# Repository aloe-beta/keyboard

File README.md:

# Keyboard

A low-profile split keyboard with 56 hotswappable, RGB backlit keys. Powered by an ESP32-S3.

This is the first project I'm trying to get a PCB manufactured for. I've polished the design up to a point I'm happy with, but there might be mistakes.

The directory structure should be self-explanatory. Currently, `firmare/` only contains a blink program. I'm still deciding whether I should try porting ZMK (ESP32-S3 requires some work) or writing my own firmware from scratch. The latter option would give me more freedom to experiment with the hardware (I have some unconventional ideas), so I'm leaning towards that.

The BOM does not contain anything for the housing or keycaps, as I intend to resin-print those myself.

**Schematic:**

**PCB:**

**Housing:**

**Keycaps:**

**BOM:**

| Name                                            | Description                                                           | Reference | Link                                                                                                          | Quantity | Unit quantity | Unit price     | Total price | Seller  |
| ----------------------------------------------- | --------------------------------------------------------------------- | --------- | ------------------------------------------------------------------------------------------------------------- | -------- | ------------- | -------------- | ----------- | ------- |
| 3.7V 1000mAh 502450 Lipo                        | Battery                                                               | N/A       | https://www.amazon.com/dp/B07BTV3W87                                                                          | 2        | 2             | 7.4900         | 14.98       | Amazon  |
| CL31A107MQHNNWE                                 | 100uF capacitor for the LEDs                                          | C1-C2     | https://www.digikey.com/en/products/detail/samsung-electro-mechanics/CL31A107MQHNNWE/10479833                 | 2        | 2             | 0.4000         | 0.80        | DigiKey |
| MSE1PG-M3                                       | Diodes for use in the wired interconnect                              | D113-D114 | https://www.digikey.com/en/products/detail/vishay-general-semiconductor-diodes-division/MSE1PG-M3-89A/2149917 | 2        | 2             | 0.1000         | 0.20        | DigiKey |
| 5149-LSH-3956D-005-G-19CT-ND                    | TRRS jacks for wired interconnect                                     | J1-J2     | https://www.digikey.com/en/products/detail/linkplex/LSH-3956D-005-G-19/26798666                               | 2        | 2             | 0.9900         | 1.98        | DigiKey |
| 4786-GSFC02501CT-ND                             | P-channel MOSFETs to toggle power to the LEDs and wired interconnect. | Q1-Q4     | https://www.digikey.com/en/products/detail/good-ark-semiconductor/GSFC02501/18648296                          | 4        | 10            | 0.0390         | 0.39        | DigiKey |
| 311-390GRCT-ND                                  | 390 ohm resistors for the first neopixel input lines                  | R1-R2     | https://www.digikey.com/en/products/detail/yageo/RC0603JR-07390RL/726777                                      | 2        | 10            | 0.0070         | 0.07        | DigiKey |
| 311-10.0KFRCT-ND                                | 10k ohm pull-up/pull-down resistors for MOSFET circuits               | R3-R10    | https://www.digikey.com/en/products/detail/yageo/RC1206FR-0710KL/728483                                       | 8        | 10            | 0.0180         | 0.18        | DigiKey |
| 455-1719-ND                                     | JST battery connector                                                 | TP1-TP2   | https://www.digikey.com/en/products/detail/jst-sales-america-inc/S2B-PH-K-S/926626                            | 2        | 2             | 0.1000         | 0.20        | DigiKey |
| Seeed Studio XIAO ESP32-S3                      | MCU                                                                   | U3-U4     | https://www.digikey.com/en/products/detail/seeed-technology-co-ltd/113991114/19285530                         | 2        | 2             | 7.4900         | 14.98       | DigiKey |
| GATERON Upgrade Hot-swap PCB 2.0 Socket         | Hotswappable switch bracket                                           | SW1-SW56  | https://www.gateron.com/products/gateron-hot-swap-pcb-socket?VariantsId=10170                                 | 56       | 1x70          | 7.0000         | 7.00        | Gateron |
| GATERON KS-33 Low Profile 2.0 Mechanical Switch | Low-profile mechanical switch                                         | N/A       | https://www.gateron.com/products/gateron-ks-33-low-profile-switch-set?VariantsId=11464                        | 56       | 2x35          | 9.8000         | 19.60       | Gateron |
| PCB                                             | The circuit board for the keyboard.                                   | N/A       | N/A                                                                                                           | 1        | 1x5           | 21.8600        | 11.00       | JLC     |
| Stencil                                         | The stencil for soldering the board.                                  | N/A       | N/A                                                                                                           | 1        | 1             | 7.0000         | 7.00        | JLC     |
| 1N4148W                                         | Diodes to prevent key ghosting                                        | D1-D56    | https://www.lcsc.com/product-detail/C51953478.html                                                            | 56       | 56            | 0.0430         | 2.41        | LCSC    |
| SK6812MINI-E                                    | Addressable RGB LEDs for the backlight                                | D57-D112  | https://www.lcsc.com/product-detail/C5149201.html                                                             | 56       | 60            | 0.0683         | 4.10        | LCSC    |
| SK12D07VG5                                      | Power switches                                                        | SW57-SW58 | https://www.lcsc.com/product-detail/C3020419.html                                                             | 2        | 20            | 0.0210         | 0.42        | LCSC    |
|                                                 |                                                                       |           |                                                                                                               |          |               | Tariffs        | 1.50        | DigiKey |
|                                                 |                                                                       |           |                                                                                                               |          |               | Shipping       | 4.99        | DigiKey |
|                                                 |                                                                       |           |                                                                                                               |          |               | Service Charge | 1.55        | Gateron |
|                                                 |                                                                       |           |                                                                                                               |          |               | Shipping       | 8.60        | Gateron |
|                                                 |                                                                       |           |                                                                                                               |          |               | Shipping       | 29.22       | JLC     |
|                                                 |                                                                       |           |                                                                                                               |          |               | Handling Fee   | 3.00        | LCSC    |
|                                                 |                                                                       |           |                                                                                                               |          |               | Shipping       | 8.42        | LCSC    |
|                                                 |                                                                       |           |                                                                                                               |          |               | Sales Tax      | 7.84        |         |
|                                                 |                                                                       |           |                                                                                                               |          |               | Total          | 150.43      |         |

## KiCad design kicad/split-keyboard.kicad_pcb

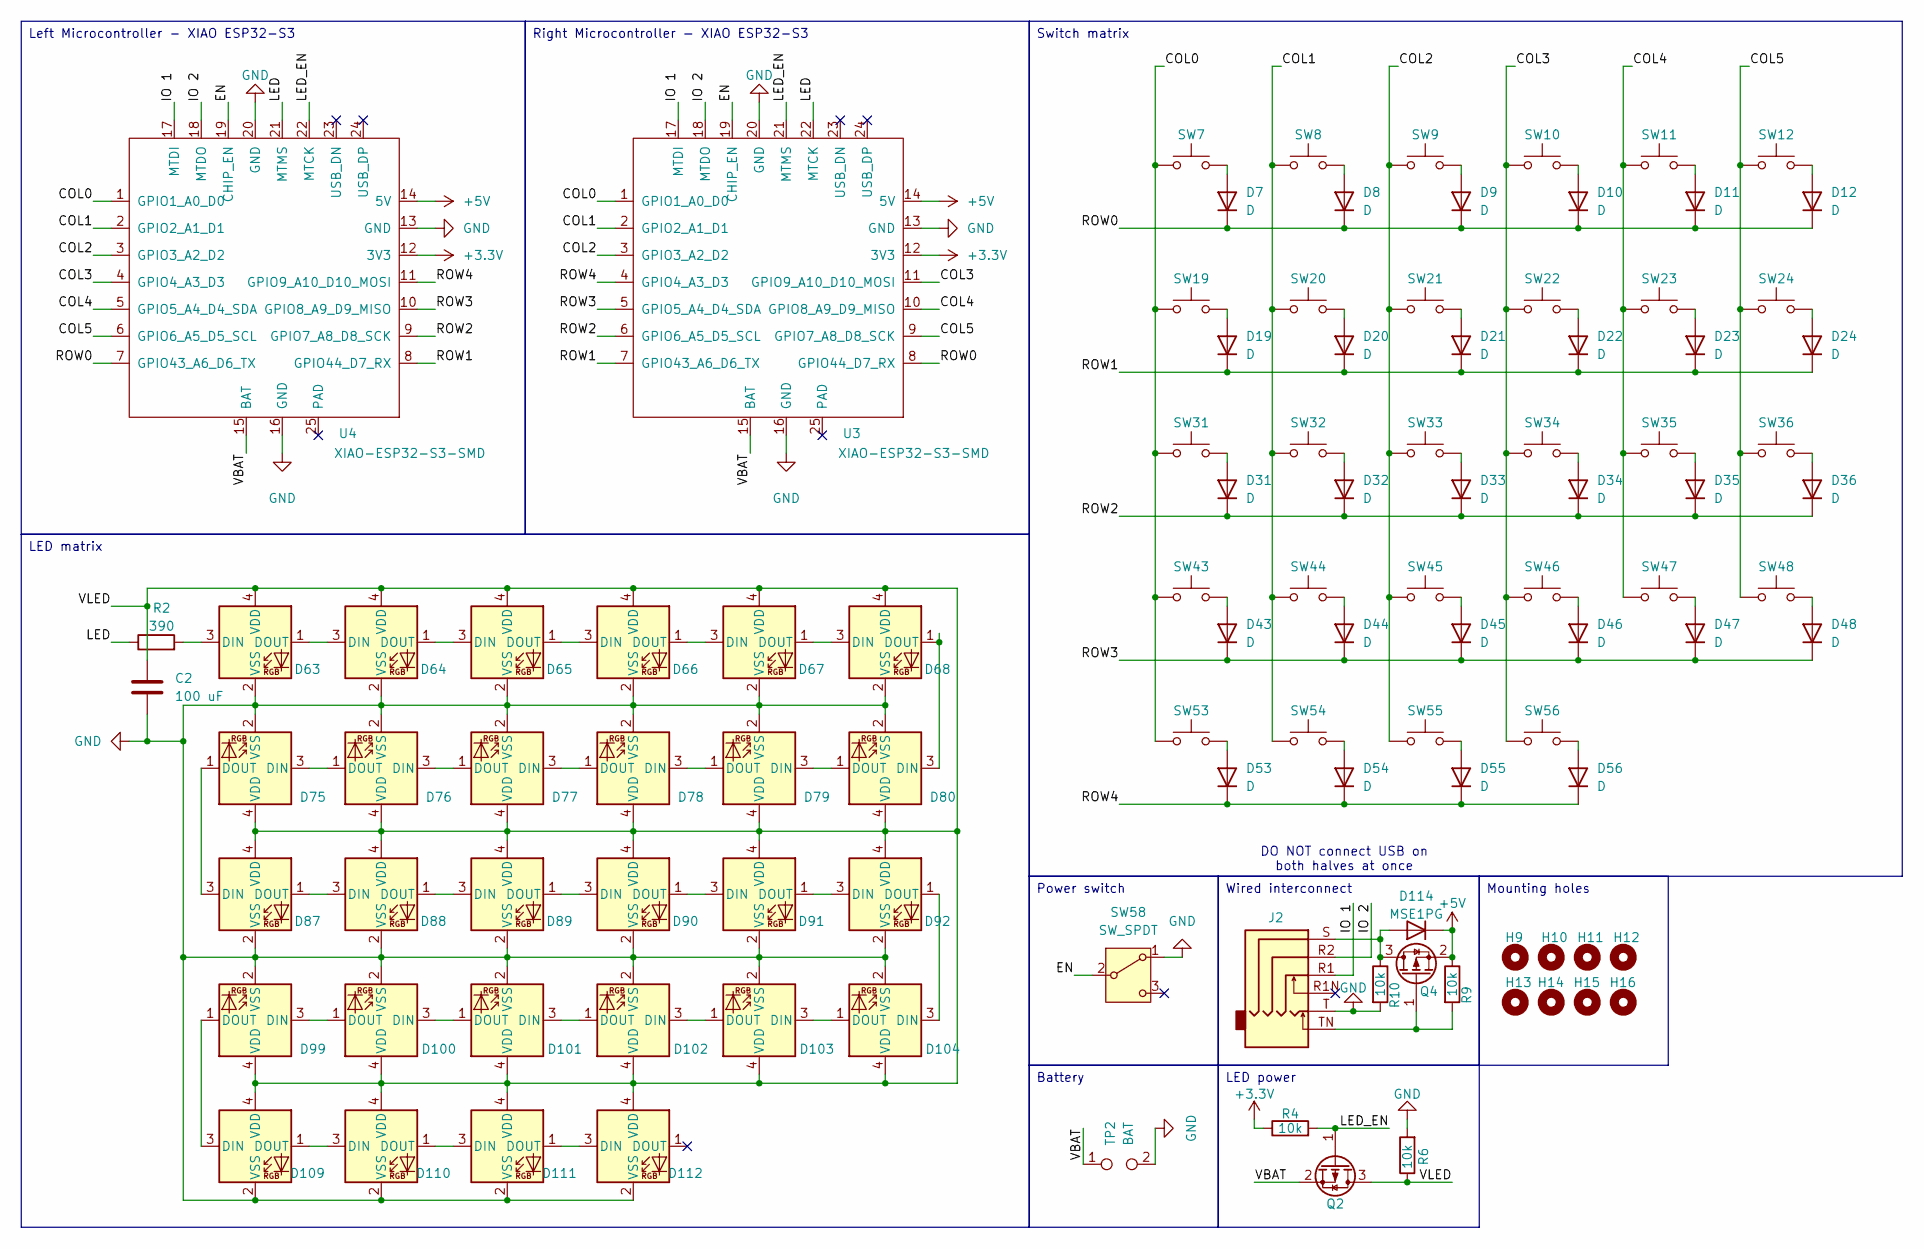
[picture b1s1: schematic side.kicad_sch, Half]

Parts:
C2: 100 uF; C_1206_3216Metric; LCSC C22399655
D7, D8, D9, D10, D11, D12, D19, D20, D21, D22, D23, D24, D31, D32, D33, D34, D35, D36, D43, D44, D45, D46, D47, D48, D53, D54, D55, D56: D; D_SOD-123; LCSC C169491
D63, D64, D65, D66, D67, D68, D75, D76, D77, D78, D79, D80, D87, D88, D89, D90, D91, D92, D99, D100, D101, D102, D103, D104, D109, D110, D111, D112: SK6812MINI; SK6812MINI-E_1-REV; LCSC C5149201
D114: MSE1PG; D_MicroSMP_AK; LCSC C94470
H9, H10, H11, H12, H13, H14, H15, H16: MountingHole; MountingHole_2.2mm_M2
J2: AudioJack4_SwitchTR1; LSH-3956D
Q2, Q4: Q_PMOS_GSD; SOT-23; LCSC C2589
R2: 390; R_0603_1608Metric; LCSC C190196
R4, R6, R9, R10: 10k; R_1206_3216Metric; LCSC C702844
SW7, SW8, SW9, SW10, SW11, SW12, SW19, SW20, SW21, SW22, SW23, SW24, SW31, SW32, SW33, SW34, SW35, SW36, SW43, SW44, SW45, SW46, SW47, SW48, SW53, SW54, SW55, SW56: SW_Push; SW_KS33_HS_KS-2P02B01-02_HS_1u; LCSC C9900205432
SW58: SW_SPDT; SK12D07VG5; LCSC C2896621
TP2: BAT; JST_PH_S2B-PH-K_1x02_P2.00mm_Horizontal; LCSC C173752
U3, U4: XIAO-ESP32-S3-SMD; XIAO-ESP32S3-SMD; LCSC C9900124959

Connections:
+3.3V: R4.1, U3.12 (3V3), U4.12 (3V3)
+5V: D114.1 (K), Q4.2 (S), R9.1, U3.14 (5V), U4.14 (5V)
/right/COL0: SW7.1, SW19.1, SW31.1, SW43.1, SW53.1, U3.1 (GPIO1_A0_D0), U4.1 (GPIO1_A0_D0)
/right/COL1: SW8.1, SW20.1, SW32.1, SW44.1, SW54.1, U3.2 (GPIO2_A1_D1), U4.2 (GPIO2_A1_D1)
/right/COL2: SW9.1, SW21.1, SW33.1, SW45.1, SW55.1, U3.3 (GPIO3_A2_D2), U4.3 (GPIO3_A2_D2)
/right/COL3: SW10.1, SW22.1, SW34.1, SW46.1, SW56.1, U3.11 (GPIO9_A10_D10_MOSI), U4.4 (GPIO4_A3_D3)
/right/COL4: SW11.1, SW23.1, SW35.1, SW47.1, U3.10 (GPIO8_A9_D9_MISO), U4.5 (GPIO5_A4_D4_SDA)
/right/COL5: SW12.1, SW24.1, SW36.1, SW48.1, U3.9 (GPIO7_A8_D8_SCK), U4.6 (GPIO6_A5_D5_SCL)
/right/EN: SW58.2 (B), U3.19 (CHIP_EN), U4.19 (CHIP_EN)
/right/IO 1: J2.R1, U3.17 (MTDI), U4.17 (MTDI)
/right/IO 2: J2.R2, U3.18 (MTDO), U4.18 (MTDO)
/right/LED: R2.1, U3.22 (MTCK), U4.21 (MTMS)
/right/LED_EN: Q2.1 (G), R4.2, U3.21 (MTMS), U4.22 (MTCK)
/right/ROW0: D7.1 (K), D8.1 (K), D9.1 (K), D10.1 (K), D11.1 (K), D12.1 (K), U3.8 (GPIO44_D7_RX), U4.7 (GPIO43_A6_D6_TX)
/right/ROW1: D19.1 (K), D20.1 (K), D21.1 (K), D22.1 (K), D23.1 (K), D24.1 (K), U3.7 (GPIO43_A6_D6_TX), U4.8 (GPIO44_D7_RX)
/right/ROW2: D31.1 (K), D32.1 (K), D33.1 (K), D34.1 (K), D35.1 (K), D36.1 (K), U3.6 (GPIO6_A5_D5_SCL), U4.9 (GPIO7_A8_D8_SCK)
/right/ROW3: D43.1 (K), D44.1 (K), D45.1 (K), D46.1 (K), D47.1 (K), D48.1 (K), U3.5 (GPIO5_A4_D4_SDA), U4.10 (GPIO8_A9_D9_MISO)
/right/ROW4: D53.1 (K), D54.1 (K), D55.1 (K), D56.1 (K), U3.4 (GPIO4_A3_D3), U4.11 (GPIO9_A10_D10_MOSI)
/right/VBAT: Q2.2 (S), TP2.1, U3.15 (BAT), U4.15 (BAT)
/right/VLED: C2.1, D63.4 (VDD), D64.4 (VDD), D65.4 (VDD), D66.4 (VDD), D67.4 (VDD), D68.4 (VDD), D75.4 (VDD), D76.4 (VDD), D77.4 (VDD), D78.4 (VDD), D79.4 (VDD), D80.4 (VDD), D87.4 (VDD), D88.4 (VDD), D89.4 (VDD), D90.4 (VDD), D91.4 (VDD), D92.4 (VDD), D99.4 (VDD), D100.4 (VDD), D101.4 (VDD), D102.4 (VDD), D103.4 (VDD), D104.4 (VDD), D109.4 (VDD), D110.4 (VDD), D111.4 (VDD), D112.4 (VDD), Q2.3 (D), R6.1
GND: C2.2, D63.2 (VSS), D64.2 (VSS), D65.2 (VSS), D66.2 (VSS), D67.2 (VSS), D68.2 (VSS), D75.2 (VSS), D76.2 (VSS), D77.2 (VSS), D78.2 (VSS), D79.2 (VSS), D80.2 (VSS), D87.2 (VSS), D88.2 (VSS), D89.2 (VSS), D90.2 (VSS), D91.2 (VSS), D92.2 (VSS), D99.2 (VSS), D100.2 (VSS), D101.2 (VSS), D102.2 (VSS), D103.2 (VSS), D104.2 (VSS), D109.2 (VSS), D110.2 (VSS), D111.2 (VSS), D112.2 (VSS), J2.T, R6.2, R10.2, SW58.1 (A), TP2.2, U3.13 (GND), U3.16 (GND), U3.20 (GND), U4.13 (GND), U4.16 (GND), U4.20 (GND)
unnamed: D7.2 (A), SW7.2
unnamed: D8.2 (A), SW8.2
unnamed: D9.2 (A), SW9.2
unnamed: D10.2 (A), SW10.2
unnamed: D11.2 (A), SW11.2
unnamed: D12.2 (A), SW12.2
unnamed: D19.2 (A), SW19.2
unnamed: D20.2 (A), SW20.2
unnamed: D21.2 (A), SW21.2
unnamed: D22.2 (A), SW22.2
unnamed: D23.2 (A), SW23.2
unnamed: D24.2 (A), SW24.2
unnamed: D31.2 (A), SW31.2
unnamed: D32.2 (A), SW32.2
unnamed: D33.2 (A), SW33.2
unnamed: D34.2 (A), SW34.2
unnamed: D35.2 (A), SW35.2
unnamed: D36.2 (A), SW36.2
unnamed: D43.2 (A), SW43.2
unnamed: D44.2 (A), SW44.2
unnamed: D45.2 (A), SW45.2
unnamed: D46.2 (A), SW46.2
unnamed: D47.2 (A), SW47.2
unnamed: D48.2 (A), SW48.2
unnamed: D53.2 (A), SW53.2
unnamed: D54.2 (A), SW54.2
unnamed: D55.2 (A), SW55.2
unnamed: D56.2 (A), SW56.2
unnamed: D63.3 (DIN), R2.2
unnamed: D63.1 (DOUT), D64.3 (DIN)
unnamed: D64.1 (DOUT), D65.3 (DIN)
unnamed: D65.1 (DOUT), D66.3 (DIN)
unnamed: D66.1 (DOUT), D67.3 (DIN)
unnamed: D67.1 (DOUT), D68.3 (DIN)
unnamed: D68.1 (DOUT), D80.3 (DIN)
unnamed: D75.3 (DIN), D76.1 (DOUT)
unnamed: D75.1 (DOUT), D87.3 (DIN)
unnamed: D76.3 (DIN), D77.1 (DOUT)
unnamed: D77.3 (DIN), D78.1 (DOUT)
unnamed: D78.3 (DIN), D79.1 (DOUT)
unnamed: D79.3 (DIN), D80.1 (DOUT)
unnamed: D87.1 (DOUT), D88.3 (DIN)
unnamed: D88.1 (DOUT), D89.3 (DIN)
unnamed: D89.1 (DOUT), D90.3 (DIN)
unnamed: D90.1 (DOUT), D91.3 (DIN)
unnamed: D91.1 (DOUT), D92.3 (DIN)
unnamed: D100.3 (DIN), D101.1 (DOUT)
unnamed: D99.3 (DIN), D100.1 (DOUT)
unnamed: D101.3 (DIN), D102.1 (DOUT)
unnamed: D102.3 (DIN), D103.1 (DOUT)
unnamed: D103.3 (DIN), D104.1 (DOUT)
unnamed: D92.1 (DOUT), D104.3 (DIN)
unnamed: D99.1 (DOUT), D109.3 (DIN)
unnamed: D109.1 (DOUT), D110.3 (DIN)
unnamed: D110.1 (DOUT), D111.3 (DIN)
unnamed: D111.1 (DOUT), D112.3 (DIN)
unnamed: D114.2 (A), J2.S, Q4.3 (D), R10.1
unnamed: J2.TN, Q4.1 (G), R9.2

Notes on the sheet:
DO NOT connect USB on both halves at once
Switch matrix
Wired interconnect
Battery
Right Microcontroller - XIAO ESP32-S3
Left Microcontroller - XIAO ESP32-S3
LED power
Power switch
LED matrix
Mounting holes

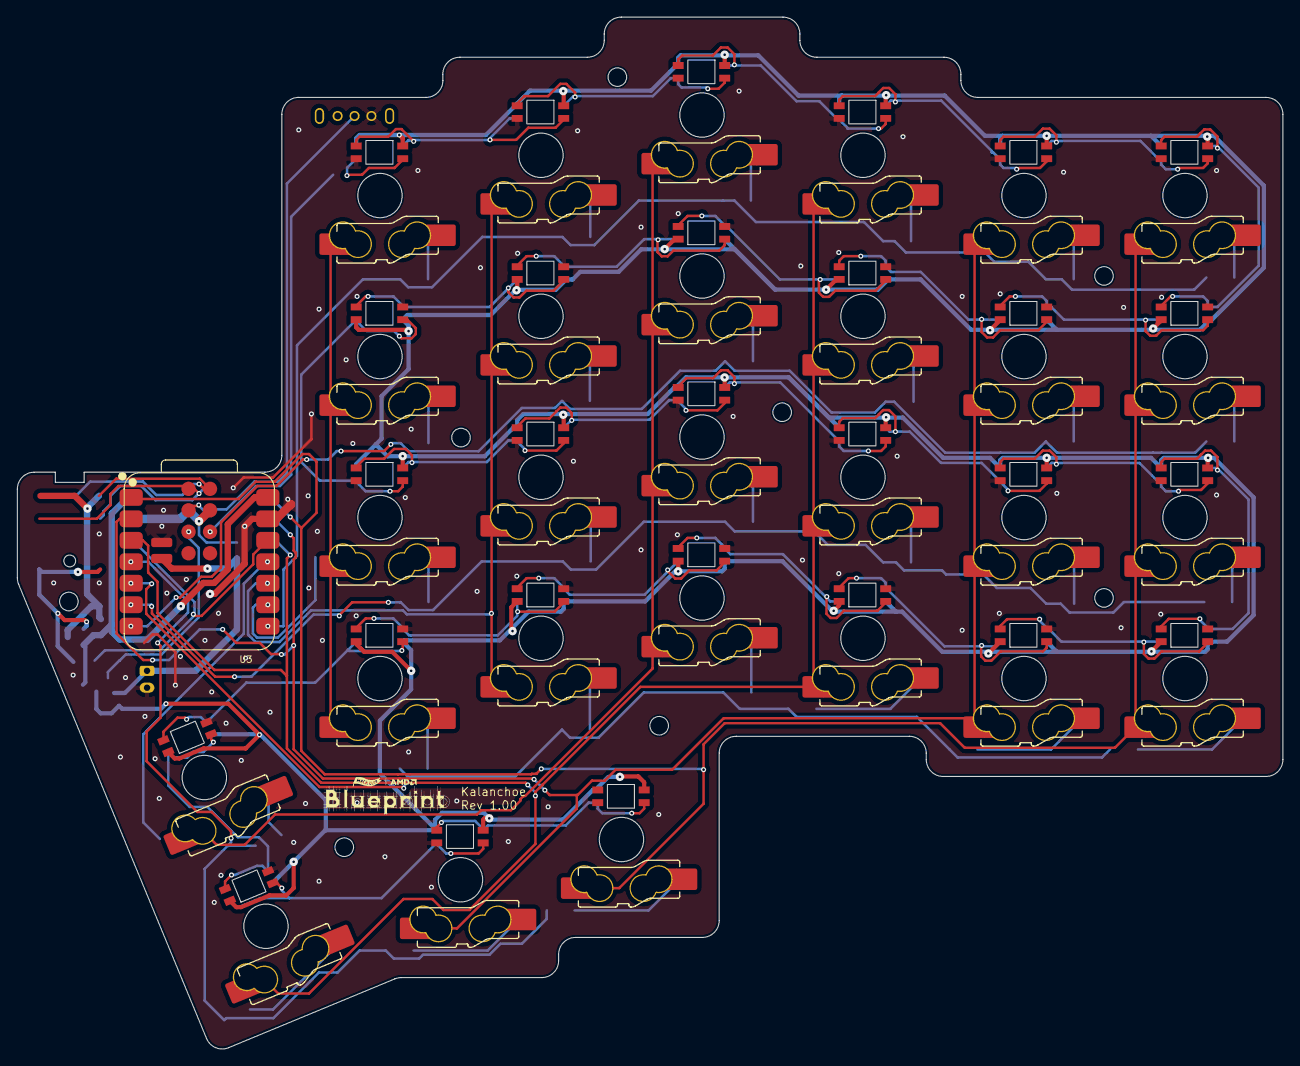
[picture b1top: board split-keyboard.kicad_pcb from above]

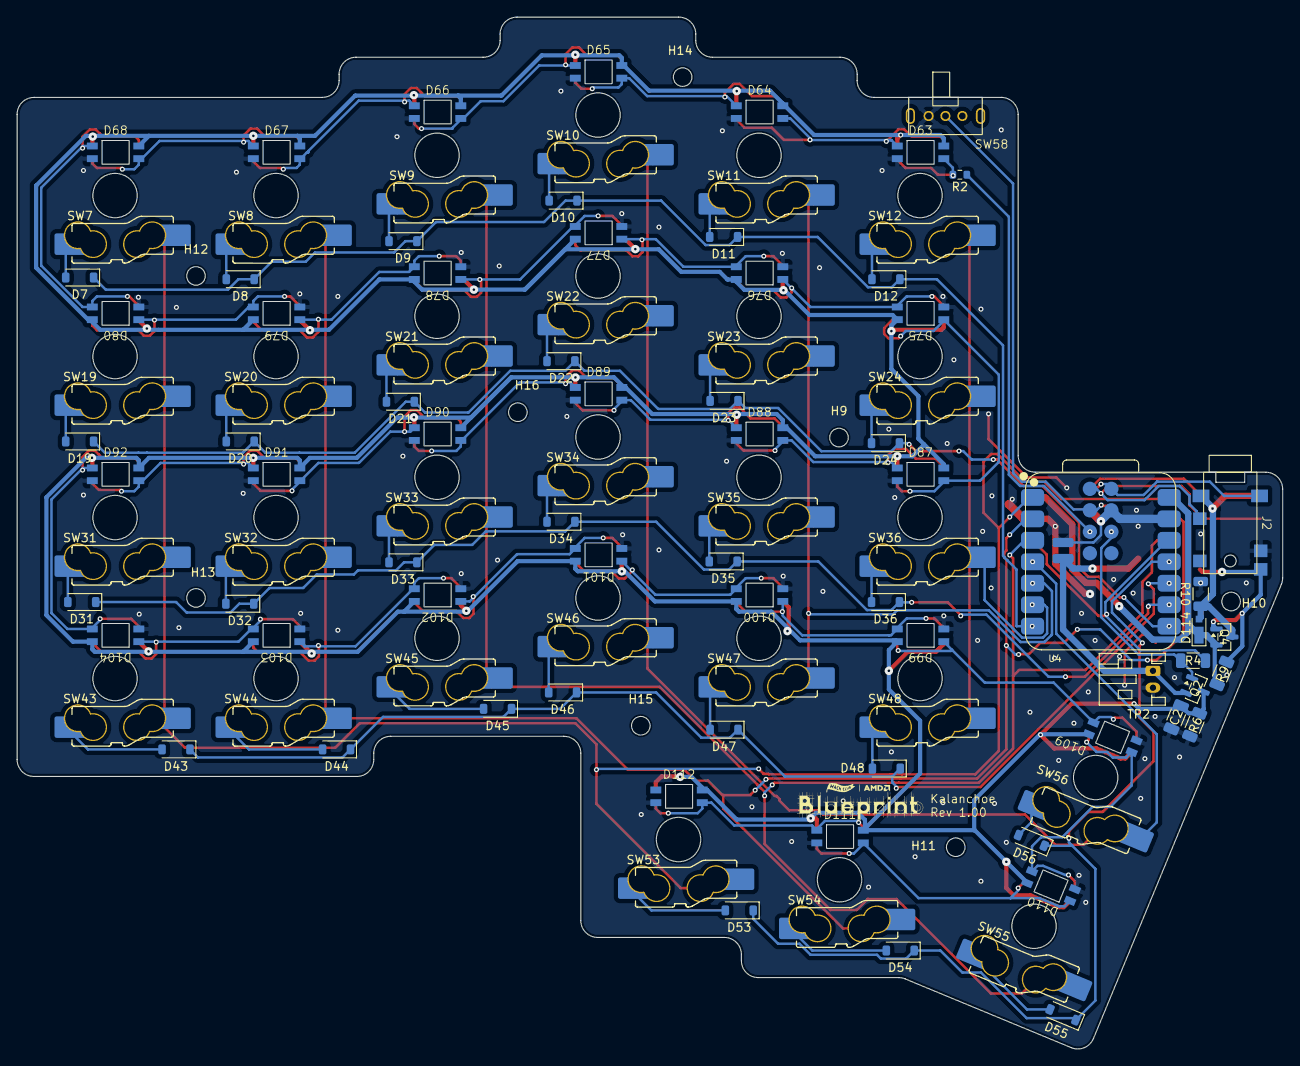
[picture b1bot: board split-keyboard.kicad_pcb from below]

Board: 2 copper layers, 149.7 x 122.0 mm, 106 parts (105 on the bottom side), 79 nets.

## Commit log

2025-10-24 Initial upload
2025-12-04 Prepared for design review
2025-12-04 Updated BOM and fixed README issue
2025-12-04 Added BOM to README
2025-12-06 Rerouted PCB
